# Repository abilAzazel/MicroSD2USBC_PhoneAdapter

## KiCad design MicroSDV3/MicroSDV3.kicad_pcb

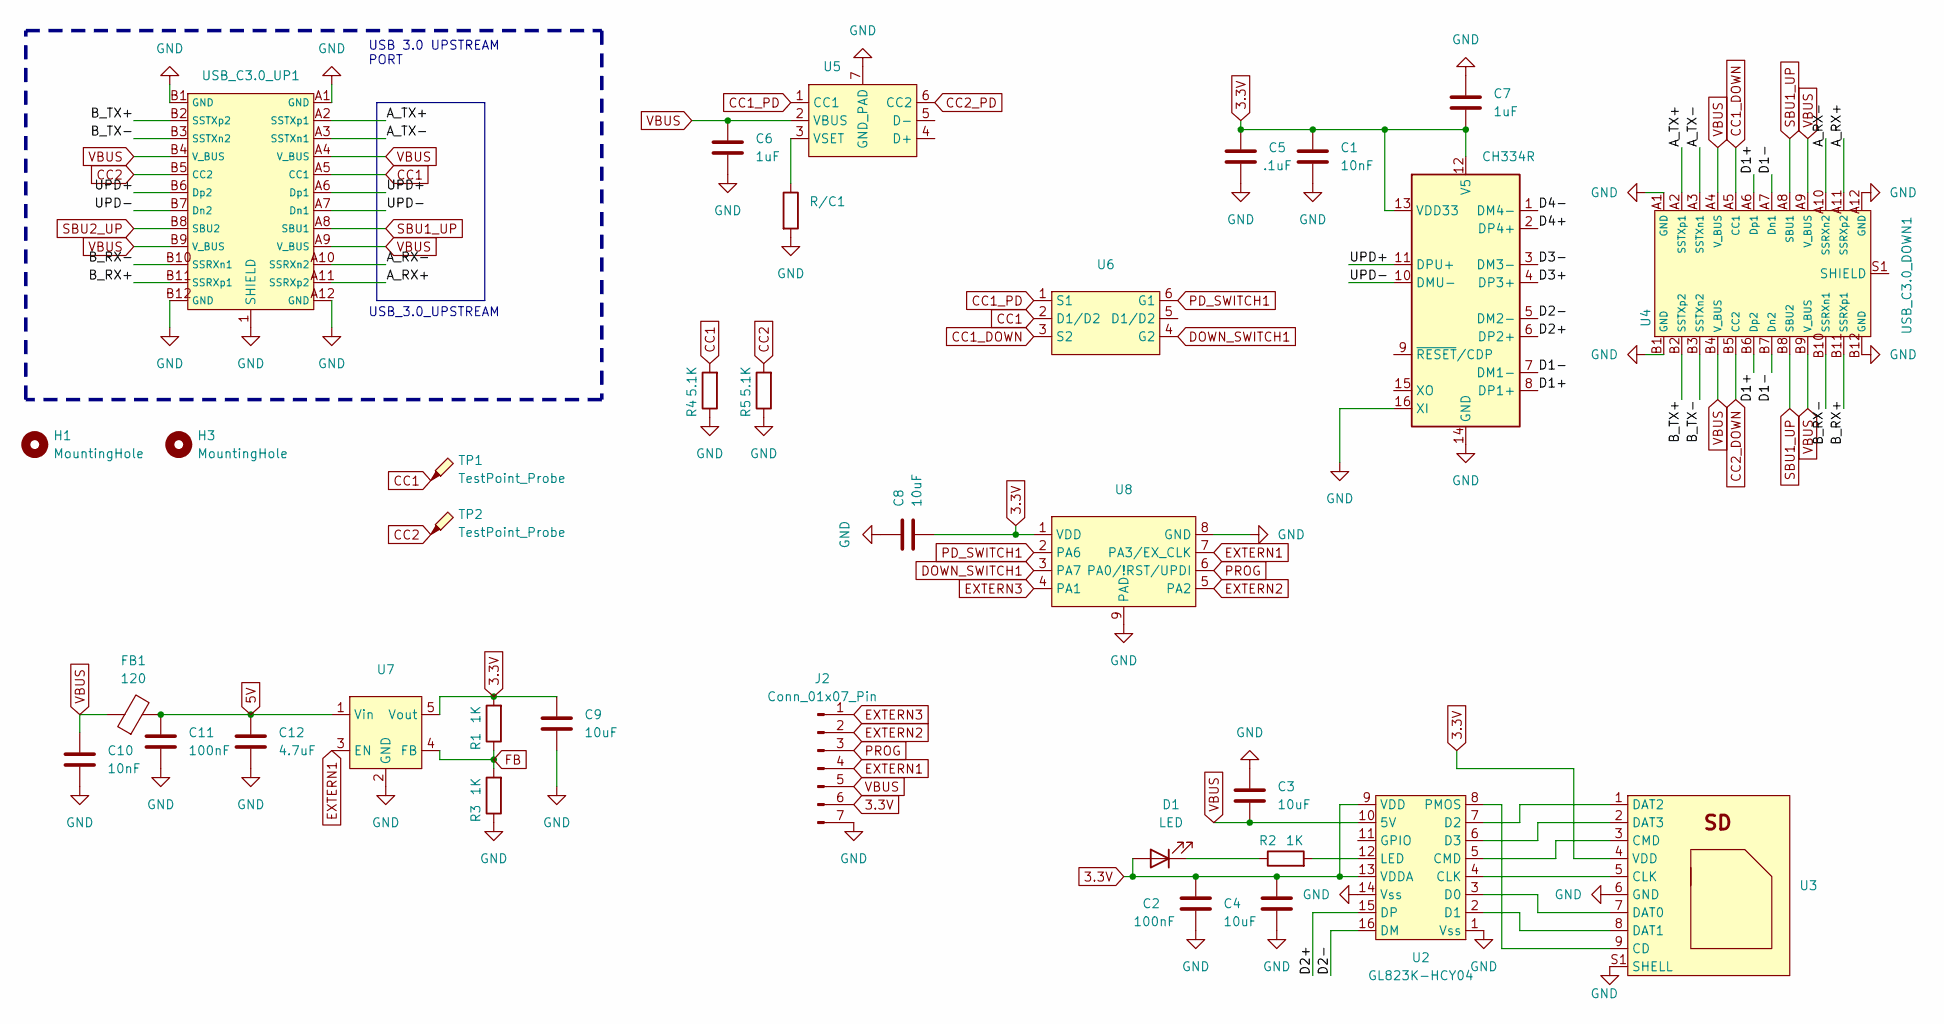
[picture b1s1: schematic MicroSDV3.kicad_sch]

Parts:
C1, C10: 10nF; C_0805_2012Metric_Pad1.18x1.45mm_HandSolder
C2, C11: 100nF; C_0805_2012Metric_Pad1.18x1.45mm_HandSolder
C3, C4, C8, C9: 10uF; C_0805_2012Metric_Pad1.18x1.45mm_HandSolder
C5: .1uF; C_0805_2012Metric_Pad1.18x1.45mm_HandSolder
C6, C7: 1uF; C_0805_2012Metric_Pad1.18x1.45mm_HandSolder
C12: 4.7uF; C_0805_2012Metric_Pad1.18x1.45mm_HandSolder
D1: LED; R_0805_2012Metric_Pad1.20x1.40mm_HandSolder
FB1: 120; R_0805_2012Metric_Pad1.20x1.40mm_HandSolder
H1, H3: MountingHole; MountingHole_3.2mm_M3
J2: Conn_01x07_Pin; PinSocket_1x07_P2.54mm_Vertical
R1, R2, R3: 1K; R_0805_2012Metric_Pad1.20x1.40mm_HandSolder
R4, R5: 5.1K; R_0805_2012Metric_Pad1.20x1.40mm_HandSolder
R/C1: C_0805_2012Metric_Pad1.18x1.45mm_HandSolder
TP1, TP2: TestPoint_Probe; TestPoint_Pad_1.0x1.0mm
U1: CH334R; QSOP-16_3.9x4.9mm_P0.635mm
U2: GL823K-HCY04; SSOP-16_3.9x4.9mm_P0.635mm
U3: TF115
U4: USB_C3.0_DOWN1; USB_C_Receptacle_Molex_105450-0101
U5: DFN-6-1EP_2x2mm_P0.65mm_EP1.01x1.7mm
U6: SOT-23-6
U7: SOT-23-5
U8: SOIC-8-1EP_3.9x4.9mm_P1.27mm_EP2.29x3mm
USB_C3.0_UP1: USB_C_Male_EdgeOUT

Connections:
5V: C11.1, C12.1, FB1.2, U7.1 (Vin)
/A_RX+: U4.A11 (SSRXp2), USB_C3.0_UP1.A11 (SSRXp2)
/A_RX-: U4.A10 (SSRXn2), USB_C3.0_UP1.A10 (SSRXn2)
/A_TX+: U4.A2 (SSTXp1), USB_C3.0_UP1.A2 (SSTXp1)
/A_TX-: U4.A3 (SSTXn1), USB_C3.0_UP1.A3 (SSTXn1)
/B_RX+: U4.B11 (SSRXp1), USB_C3.0_UP1.B11 (SSRXp1)
/B_RX-: U4.B10 (SSRXn1), USB_C3.0_UP1.B10 (SSRXn1)
/B_TX+: U4.B2 (SSTXp2), USB_C3.0_UP1.B2 (SSTXp2)
/B_TX-: U4.B3 (SSTXn2), USB_C3.0_UP1.B3 (SSTXn2)
/D1+: U1.8 (DP1+), U4.A6 (Dp1), U4.B6 (Dp2)
/D1-: U1.7 (DM1-), U4.A7 (Dn1), U4.B7 (Dn2)
/D2+: U1.6 (DP2+), U2.15 (DP)
/D2-: U1.5 (DM2-), U2.16 (DM)
/D3+: U1.4 (DP3+)
/D3-: U1.3 (DM3-)
/D4+: U1.2 (DP4+)
/D4-: U1.1 (DM4-)
/UPD+: U1.11 (DPU+), USB_C3.0_UP1.A6 (Dp1), USB_C3.0_UP1.B6 (Dp2)
/UPD-: U1.10 (DMU-), USB_C3.0_UP1.A7 (Dn1), USB_C3.0_UP1.B7 (Dn2)
CC1: R4.2, TP1.1, U6.2 (D1/D2), USB_C3.0_UP1.A5 (CC1)
CC1_DOWN: U4.A5 (CC1), U6.3 (S2)
CC1_PD: U5.1 (CC1), U6.1 (S1)
CC2: R5.2, TP2.1, USB_C3.0_UP1.B5 (CC2)
CC2_DOWN: U4.B5 (CC2)
CC2_PD: U5.6 (CC2)
DOWN_SWITCH1: U6.4 (G2), U8.3 (PA7)
EXTERN1: J2.4, U7.3 (EN), U8.7 (PA3/EX_CLK)
EXTERN2: J2.2, U8.5 (PA2)
EXTERN3: J2.1, U8.4 (PA1)
unnamed: D1.1 (K), R2.1
unnamed: U2.4 (CLK), U3.5 (CLK)
unnamed: U2.5 (CMD), U3.3 (CMD)
unnamed: U2.3 (D0), U3.7 (DAT0)
unnamed: U2.2 (D1), U3.8 (DAT1)
unnamed: U2.7 (D2), U3.1 (DAT2)
unnamed: U2.6 (D3), U3.2 (DAT3)
unnamed: R2.2, U2.12 (LED)
unnamed: U2.8 (PMOS), U3.9 (CD)
unnamed: R/C1.1, U5.3 (VSET)
PD_SWITCH1: U6.6 (G1), U8.2 (PA6)
PROG: J2.3, U8.6 (PA0/!RST/UPDI)
SBU1_UP: U4.A8 (SBU1), U4.B8 (SBU2), USB_C3.0_UP1.A8 (SBU1)
SBU2_UP: USB_C3.0_UP1.B8 (SBU2)
VBUS: C3.2, C6.1, C10.1, FB1.1, J2.5, U2.10 (5V), U4.A4 (V_BUS), U4.A9 (V_BUS), U4.B4 (V_BUS), U4.B9 (V_BUS), U5.2 (VBUS), USB_C3.0_UP1.A4 (V_BUS), USB_C3.0_UP1.A9 (V_BUS), USB_C3.0_UP1.B4 (V_BUS), USB_C3.0_UP1.B9 (V_BUS)

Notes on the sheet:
USB_3.0_UPSTREAM
USB 3.0 UPSTREAM PORT

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
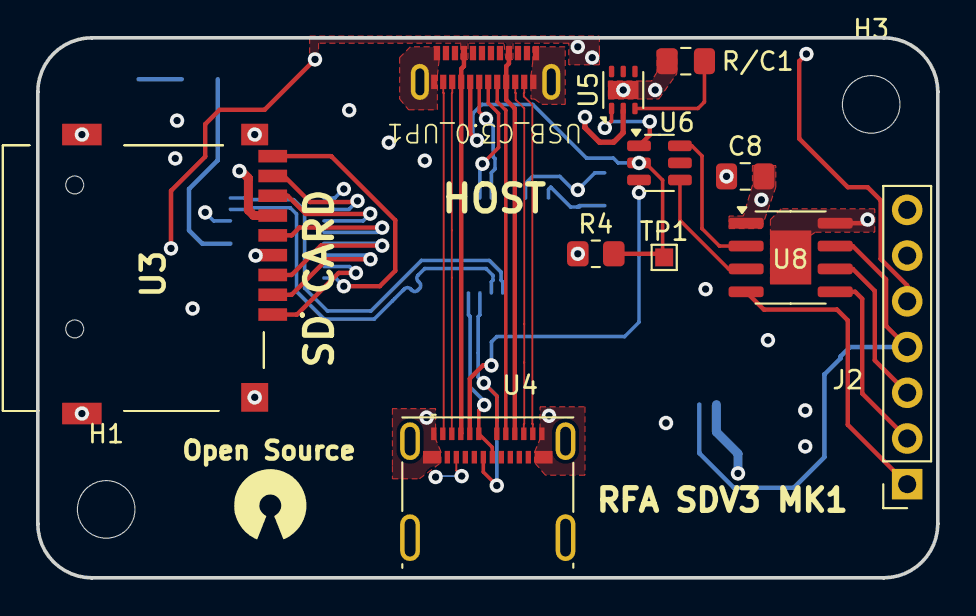
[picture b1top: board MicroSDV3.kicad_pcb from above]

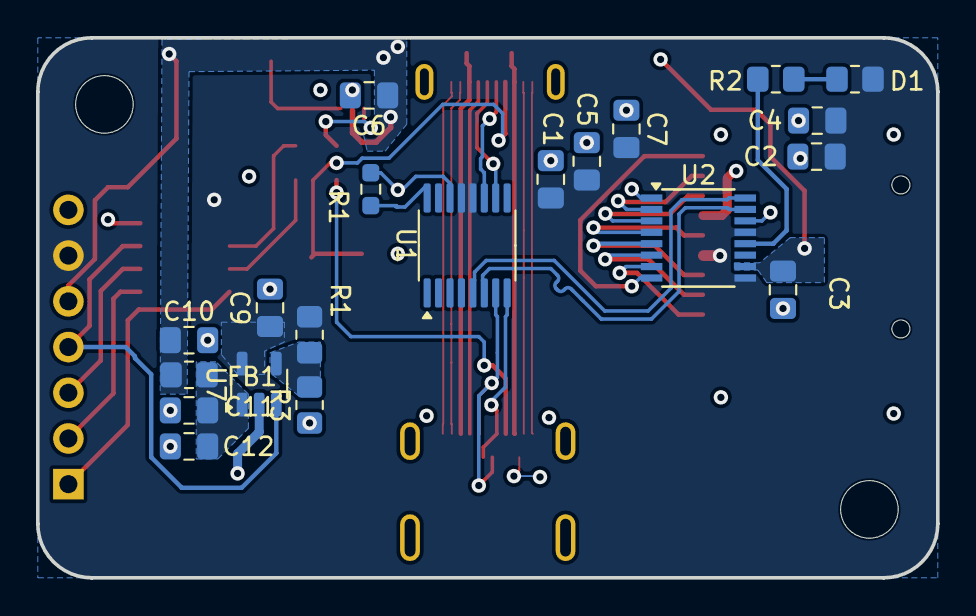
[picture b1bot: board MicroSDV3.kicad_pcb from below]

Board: 4 copper layers, 50.0 x 30.0 mm, 33 parts (20 on the bottom side), 39 nets.

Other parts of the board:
R1#2: 1K; R_0805_2012Metric_Pad1.20x1.40mm_HandSolder

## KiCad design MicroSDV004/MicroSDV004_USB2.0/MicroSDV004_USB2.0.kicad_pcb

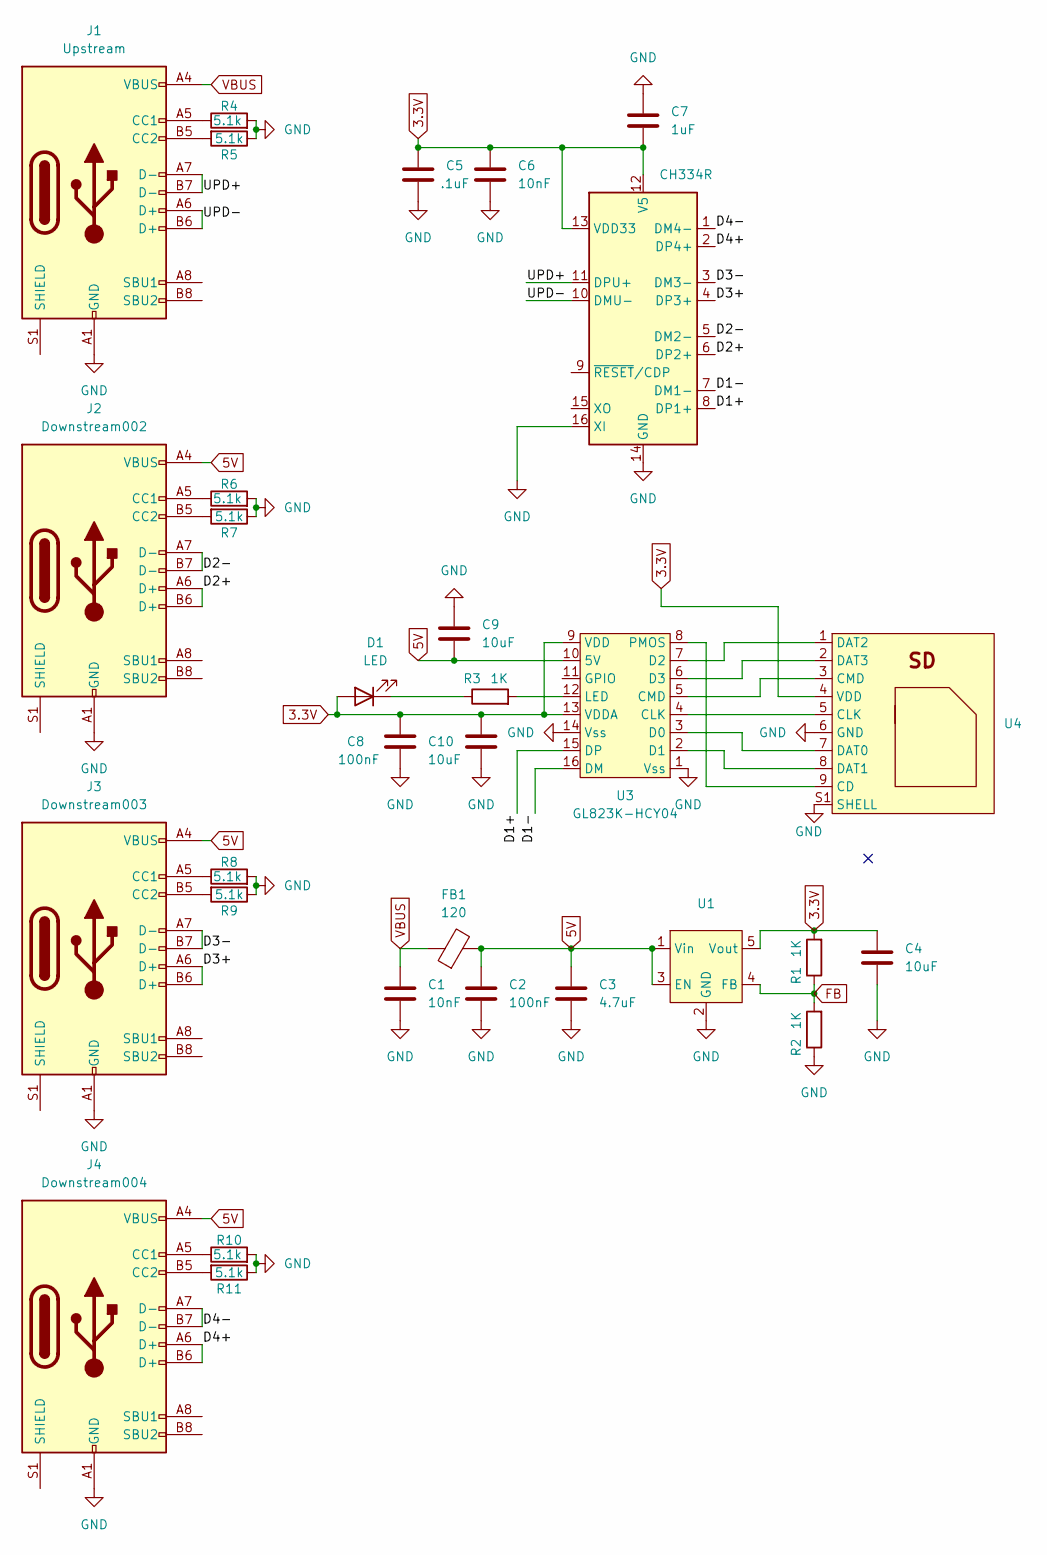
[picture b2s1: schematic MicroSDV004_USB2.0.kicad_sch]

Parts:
C1, C6: 10nF; C_0805_2012Metric_Pad1.18x1.45mm_HandSolder
C2, C8: 100nF; C_0805_2012Metric_Pad1.18x1.45mm_HandSolder
C3: 4.7uF; C_0805_2012Metric_Pad1.18x1.45mm_HandSolder
C4, C9, C10: 10uF; C_0805_2012Metric_Pad1.18x1.45mm_HandSolder
C5: .1uF; C_0805_2012Metric_Pad1.18x1.45mm_HandSolder
C7: 1uF; C_0805_2012Metric_Pad1.18x1.45mm_HandSolder
D1: LED; R_0805_2012Metric_Pad1.20x1.40mm_HandSolder
FB1: 120; R_0805_2012Metric_Pad1.20x1.40mm_HandSolder
J1: Upstream; USB_C_Receptacle_G-Switch_GT-USB-7010ASV
J2: Downstream002; USB_C_Receptacle_G-Switch_GT-USB-7010ASV
J3: Downstream003; USB_C_Receptacle_G-Switch_GT-USB-7010ASV
J4: Downstream004; USB_C_Receptacle_G-Switch_GT-USB-7010ASV
R1, R2, R3: 1K; R_0805_2012Metric_Pad1.20x1.40mm_HandSolder
R4, R5, R6, R7, R8, R9, R10, R11: 5.1k; R_0805_2012Metric_Pad1.20x1.40mm_HandSolder
U1: SOT-23-5
U2: CH334R; QSOP-16_3.9x4.9mm_P0.635mm
U3: GL823K-HCY04; SSOP-16_3.9x4.9mm_P0.635mm
U4: TF115

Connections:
3.3V: C4.1, C5.1, C6.1, C7.2, C8.1, C10.1, D1.2 (A), R1.2, U1.5 (Vout), U2.12 (V5), U2.13 (VDD33), U3.9 (VDD), U3.13 (VDDA), U4.4 (VDD)
5V: C2.1, C3.1, C9.2, FB1.2, J2.A4 (VBUS), J2.A9 (VBUS), J2.B4 (VBUS), J2.B9 (VBUS), J3.A4 (VBUS), J3.A9 (VBUS), J3.B4 (VBUS), J3.B9 (VBUS), J4.A4 (VBUS), J4.A9 (VBUS), J4.B4 (VBUS), J4.B9 (VBUS), U1.1 (Vin), U1.3 (EN), U3.10 (5V)
/D1+: U2.8 (DP1+), U3.15 (DP)
/D1-: U2.7 (DM1-), U3.16 (DM)
/D2+: J2.A6 (D+), J2.B6 (D+), U2.6 (DP2+)
/D2-: J2.A7 (D-), J2.B7 (D-), U2.5 (DM2-)
/D3+: J3.A6 (D+), J3.B6 (D+), U2.4 (DP3+)
/D3-: J3.A7 (D-), J3.B7 (D-), U2.3 (DM3-)
/D4+: J4.A6 (D+), J4.B6 (D+), U2.2 (DP4+)
/D4-: J4.A7 (D-), J4.B7 (D-), U2.1 (DM4-)
/UPD+: J1.A7 (D-), J1.B7 (D-), U2.11 (DPU+)
/UPD-: J1.A6 (D+), J1.B6 (D+), U2.10 (DMU-)
FB: R1.1, R2.2, U1.4 (FB)
GND: C1.2, C2.2, C3.2, C4.2, C5.2, C6.2, C7.1, C8.2, C9.1, C10.2, J1.A1 (GND), J1.A12 (GND), J1.B1 (GND), J1.B12 (GND), J2.A1 (GND), J2.A12 (GND), J2.B1 (GND), J2.B12 (GND), J3.A1 (GND), J3.A12 (GND), J3.B1 (GND), J3.B12 (GND), J4.A1 (GND), J4.A12 (GND), J4.B1 (GND), J4.B12 (GND), R2.1, R4.2, R5.1, R6.2, R7.1, R8.2, R9.1, R10.2, R11.1, U1.2 (GND), U2.14 (GND), U2.16 (XI), U3.1 (Vss), U3.14 (Vss), U4.6 (GND), U4.S1 (SHELL)
unnamed: D1.1 (K), R3.1
unnamed: J1.A5 (CC1), R4.1
unnamed: J1.B5 (CC2), R5.2
unnamed: J2.A5 (CC1), R6.1
unnamed: J2.B5 (CC2), R7.2
unnamed: J3.A5 (CC1), R8.1
unnamed: J3.B5 (CC2), R9.2
unnamed: J4.A5 (CC1), R10.1
unnamed: J4.B5 (CC2), R11.2
unnamed: U3.4 (CLK), U4.5 (CLK)
unnamed: U3.5 (CMD), U4.3 (CMD)
unnamed: U3.3 (D0), U4.7 (DAT0)
unnamed: U3.2 (D1), U4.8 (DAT1)
unnamed: U3.7 (D2), U4.1 (DAT2)
unnamed: U3.6 (D3), U4.2 (DAT3)
unnamed: R3.2, U3.12 (LED)
unnamed: U3.8 (PMOS), U4.9 (CD)
VBUS: C1.1, FB1.1, J1.A4 (VBUS), J1.A9 (VBUS), J1.B4 (VBUS), J1.B9 (VBUS)

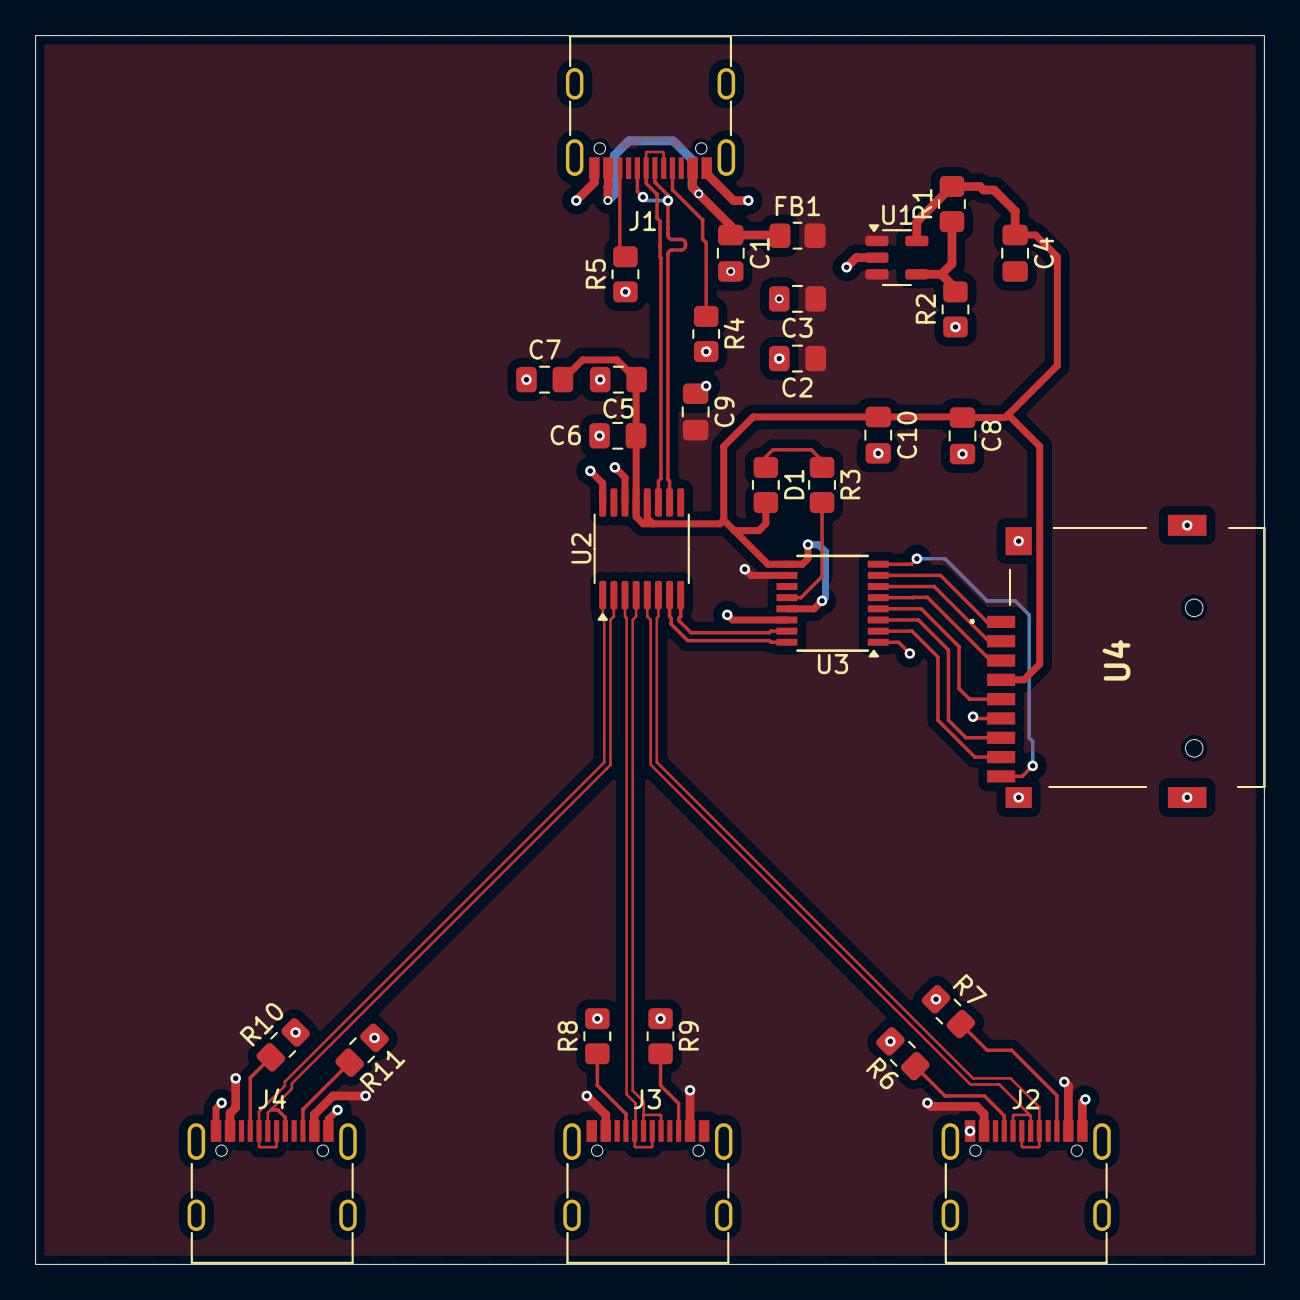
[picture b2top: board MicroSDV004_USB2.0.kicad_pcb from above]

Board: 2 copper layers, 70.0 x 70.0 mm, 31 parts (0 on the bottom side), 32 nets.

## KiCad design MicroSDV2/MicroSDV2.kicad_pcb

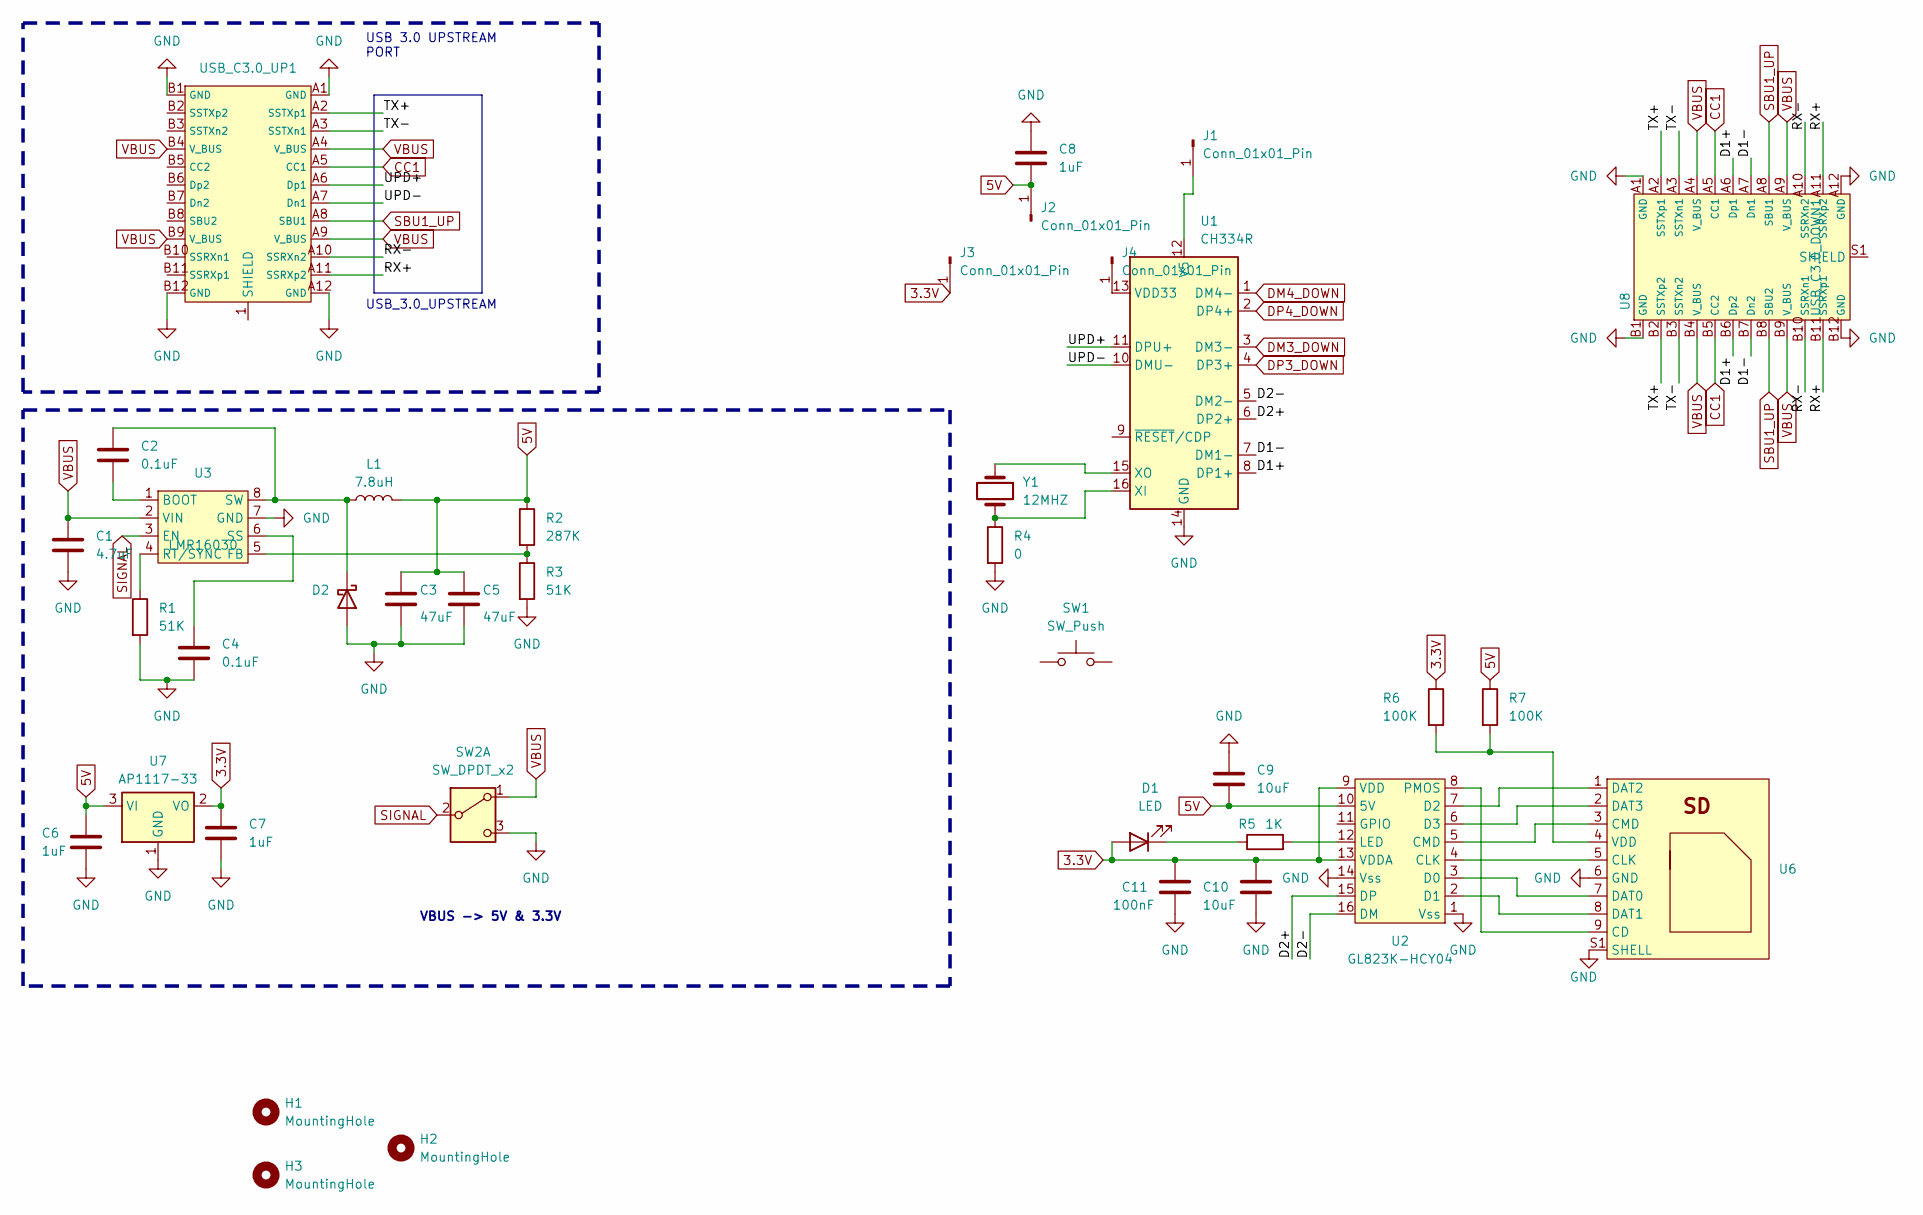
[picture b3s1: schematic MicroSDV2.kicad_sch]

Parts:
C1: 4.7uF; C_1210_3225Metric
C2, C4: 0.1uF; C_0805_2012Metric
C3, C5: 47uF; C_1210_3225Metric_Pad1.33x2.70mm_HandSolder
C6, C7, C8: 1uF; C_0805_2012Metric_Pad1.18x1.45mm_HandSolder
C9, C10: 10uF; C_0805_2012Metric_Pad1.18x1.45mm_HandSolder
C11: 100nF; C_0805_2012Metric_Pad1.18x1.45mm_HandSolder
D1: LED; R_0805_2012Metric_Pad1.20x1.40mm_HandSolder
D2: 771-PMEG6030EP-115; D_SOD-128
H1, H2, H3: MountingHole; MountingHole_3.2mm_M3
J1, J2, J3, J4: Conn_01x01_Pin; PinHeader_1x01_P1.00mm_Vertical
L1: 7.8uH; L_Bourns_SRN6045TA
R1, R3: 51K; R_0805_2012Metric_Pad1.20x1.40mm_HandSolder
R2: 287K; R_0805_2012Metric_Pad1.20x1.40mm_HandSolder
R4: 0; R_0603_1608Metric_Pad0.98x0.95mm_HandSolder
R5: 1K; R_0805_2012Metric_Pad1.20x1.40mm_HandSolder
R6, R7: 100K; R_0603_1608Metric_Pad0.98x0.95mm_HandSolder
SW1: SW_Push
SW2: SW_DPDT_x2; PinHeader_1x03_P2.54mm_Vertical
U1: CH334R; QSOP-16_3.9x4.9mm_P0.635mm
U2: GL823K-HCY04; SSOP-16_3.9x4.9mm_P0.635mm
U3: LMR16030; Texas_HSOP-8-1EP_3.9x4.9mm_P1.27mm
U6: TF115
U7: AP1117-33; SOT-223-3_TabPin2
U8: USB_C3.0_DOWN1; USB4080-03-A
USB_C3.0_UP1: USB_C_Male_EdgeOUT
Y1: 12MHZ; Crystal_SMD_ECS_CSM3X-2Pin_7.6x4.1mm

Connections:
3.3V: C7.1, C10.1, C11.1, D1.2 (A), J3.1, R6.1, U2.9 (VDD), U2.13 (VDDA), U7.2 (VO)
5V: C3.1, C5.1, C6.2, C8.2, C9.2, J2.1, L1.2, R2.1, R7.1, U2.10 (5V), U7.3 (VI)
/D1+: U1.8 (DP1+), U8.A6 (Dp1), U8.B6 (Dp2)
/D1-: U1.7 (DM1-), U8.A7 (Dn1), U8.B7 (Dn2)
/D2+: U1.6 (DP2+), U2.15 (DP)
/D2-: U1.5 (DM2-), U2.16 (DM)
/RX+: U8.A11 (SSRXp2), U8.B11 (SSRXp1), USB_C3.0_UP1.A11 (SSRXp2)
/RX-: U8.A10 (SSRXn2), U8.B10 (SSRXn1), USB_C3.0_UP1.A10 (SSRXn2)
/TX+: U8.A2 (SSTXp1), U8.B2 (SSTXp2), USB_C3.0_UP1.A2 (SSTXp1)
/TX-: U8.A3 (SSTXn1), U8.B3 (SSTXn2), USB_C3.0_UP1.A3 (SSTXn1)
/UPD+: U1.11 (DPU+), USB_C3.0_UP1.A6 (Dp1)
/UPD-: U1.10 (DMU-), USB_C3.0_UP1.A7 (Dn1)
CC1: U8.A5 (CC1), U8.B5 (CC2), USB_C3.0_UP1.A5 (CC1)
DM3_DOWN: U1.3 (DM3-)
DM4_DOWN: U1.1 (DM4-)
DP3_DOWN: U1.4 (DP3+)
DP4_DOWN: U1.2 (DP4+)
GND: C1.2, C3.2, C4.2, C5.2, C6.1, C7.2, C8.1, C9.1, C10.2, C11.2, D2.2 (A), R1.2, R3.2, R4.2, SW2.3 (C), U1.14 (GND), U2.1 (Vss), U2.14 (Vss), U3.7 (GND), U6.6 (GND), U6.S1 (SHELL), U7.1 (GND), U8.A1 (GND), U8.A12 (GND), U8.B1 (GND), U8.B12 (GND), USB_C3.0_UP1.A1 (GND), USB_C3.0_UP1.A12 (GND), USB_C3.0_UP1.B1 (GND), USB_C3.0_UP1.B12 (GND)
unnamed: D1.1 (K), R5.1
unnamed: C2.1, D2.1 (K), L1.1, U3.8 (SW)
unnamed: J1.1, U1.12 (V5)
unnamed: J4.1, U1.13 (VDD33)
unnamed: R4.1, U1.16 (XI), Y1.2
unnamed: U1.15 (XO), Y1.1
unnamed: U2.4 (CLK), U6.5 (CLK)
unnamed: U2.5 (CMD), U6.3 (CMD)
unnamed: U2.3 (D0), U6.7 (DAT0)
unnamed: U2.2 (D1), U6.8 (DAT1)
unnamed: U2.7 (D2), U6.1 (DAT2)
unnamed: U2.6 (D3), U6.2 (DAT3)
unnamed: R5.2, U2.12 (LED)
unnamed: U2.8 (PMOS), U6.9 (CD)
unnamed: C2.2, U3.1 (BOOT)
unnamed: R2.2, R3.1, U3.5 (FB)
unnamed: R1.1, U3.4 (RT/SYNC)
unnamed: C4.1, U3.6 (SS)
unnamed: R6.2, R7.2, U6.4 (VDD)
SBU1_UP: U8.A8 (SBU1), U8.B8 (SBU2), USB_C3.0_UP1.A8 (SBU1)
SIGNAL: SW2.2 (B), U3.3 (EN)
VBUS: C1.1, SW2.1 (A), U3.2 (VIN), U8.A4 (V_BUS), U8.A9 (V_BUS), U8.B4 (V_BUS), U8.B9 (V_BUS), USB_C3.0_UP1.A4 (V_BUS), USB_C3.0_UP1.A9 (V_BUS), USB_C3.0_UP1.B4 (V_BUS), USB_C3.0_UP1.B9 (V_BUS)

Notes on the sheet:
USB 3.0 UPSTREAM PORT
VBUS -> 5V & 3.3V
USB_3.0_UPSTREAM

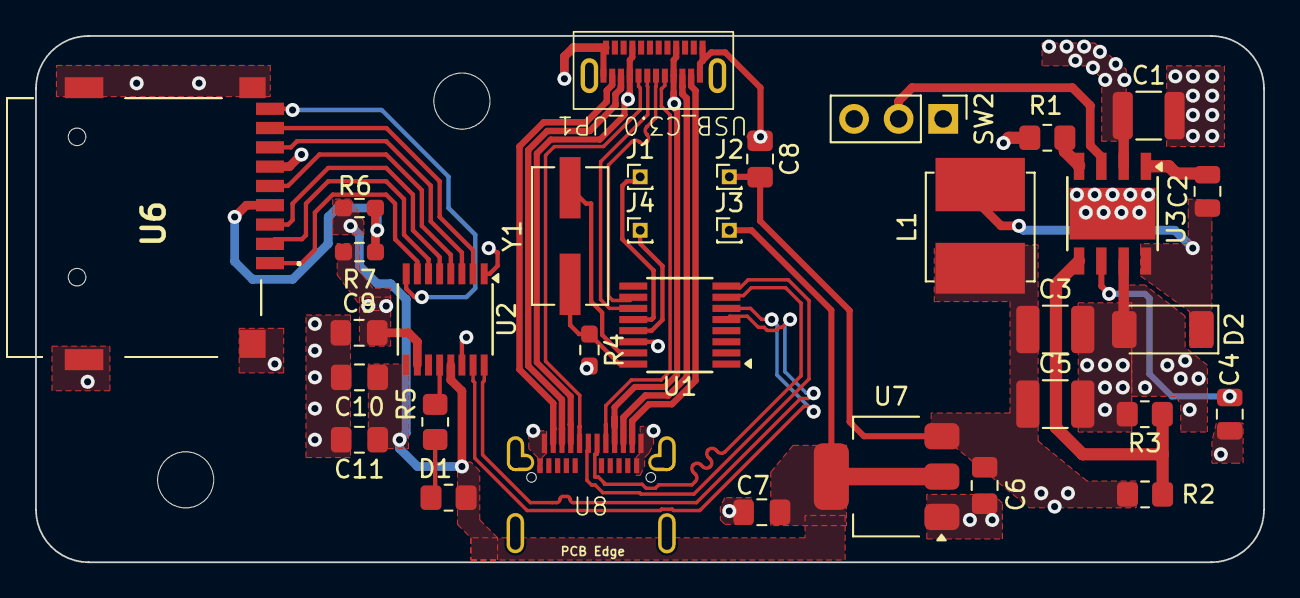
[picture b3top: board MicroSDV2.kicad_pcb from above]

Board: 2 copper layers, 70.0 x 30.0 mm, 36 parts (0 on the bottom side), 36 nets.
